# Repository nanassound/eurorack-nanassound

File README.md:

# Nanas Sound's Eurorack Modules

Modules made by Nanas Sound.
- [Mini](https://github.com/bepitulaz/eurorack-nanassound/tree/main/Mini): USB-C power supply
- [Rohkem](https://github.com/bepitulaz/eurorack-nanassound/tree/main/Rohkem): 1x7 or 2x3 passive signal multiplier
- [Uksed](https://github.com/bepitulaz/eurorack-nanassound/tree/main/Uksed): 4-channels audio input module
- [EuroPlatvorm](https://github.com/bepitulaz/eurorack-nanassound/tree/main/EuroPlatvorm): ESP32-C6 motherboard with GPIO and power breakout headers

## License

Hardware is licensed under [CC BY-SA 4.0](https://creativecommons.org/licenses/by-sa/4.0/).

By [Asep Bagja](https://www.asepbagja.com/)

Contact: [asep@nanas.ee](mailto:asep@nanas.ee)

© 2026 Nanas Sound OÜ

## Guidelines for derivative works

**Nanas Sound** is a business name of [Nanas Sound OÜ](https://ariregister.rik.ee/est/company/16028176/Nanas-Sound-OÜ).

You should not use Nanas Sound name, logo, or any other identifiers on your derivative works you create from files in this repository.

For example, your adaptation of Nanas Sound's Mini should be named "Strawberry Field - Mini Fruity" or similar.

You should include a visible license notice as required by the terms of the CC BY-SA 4.0 license.

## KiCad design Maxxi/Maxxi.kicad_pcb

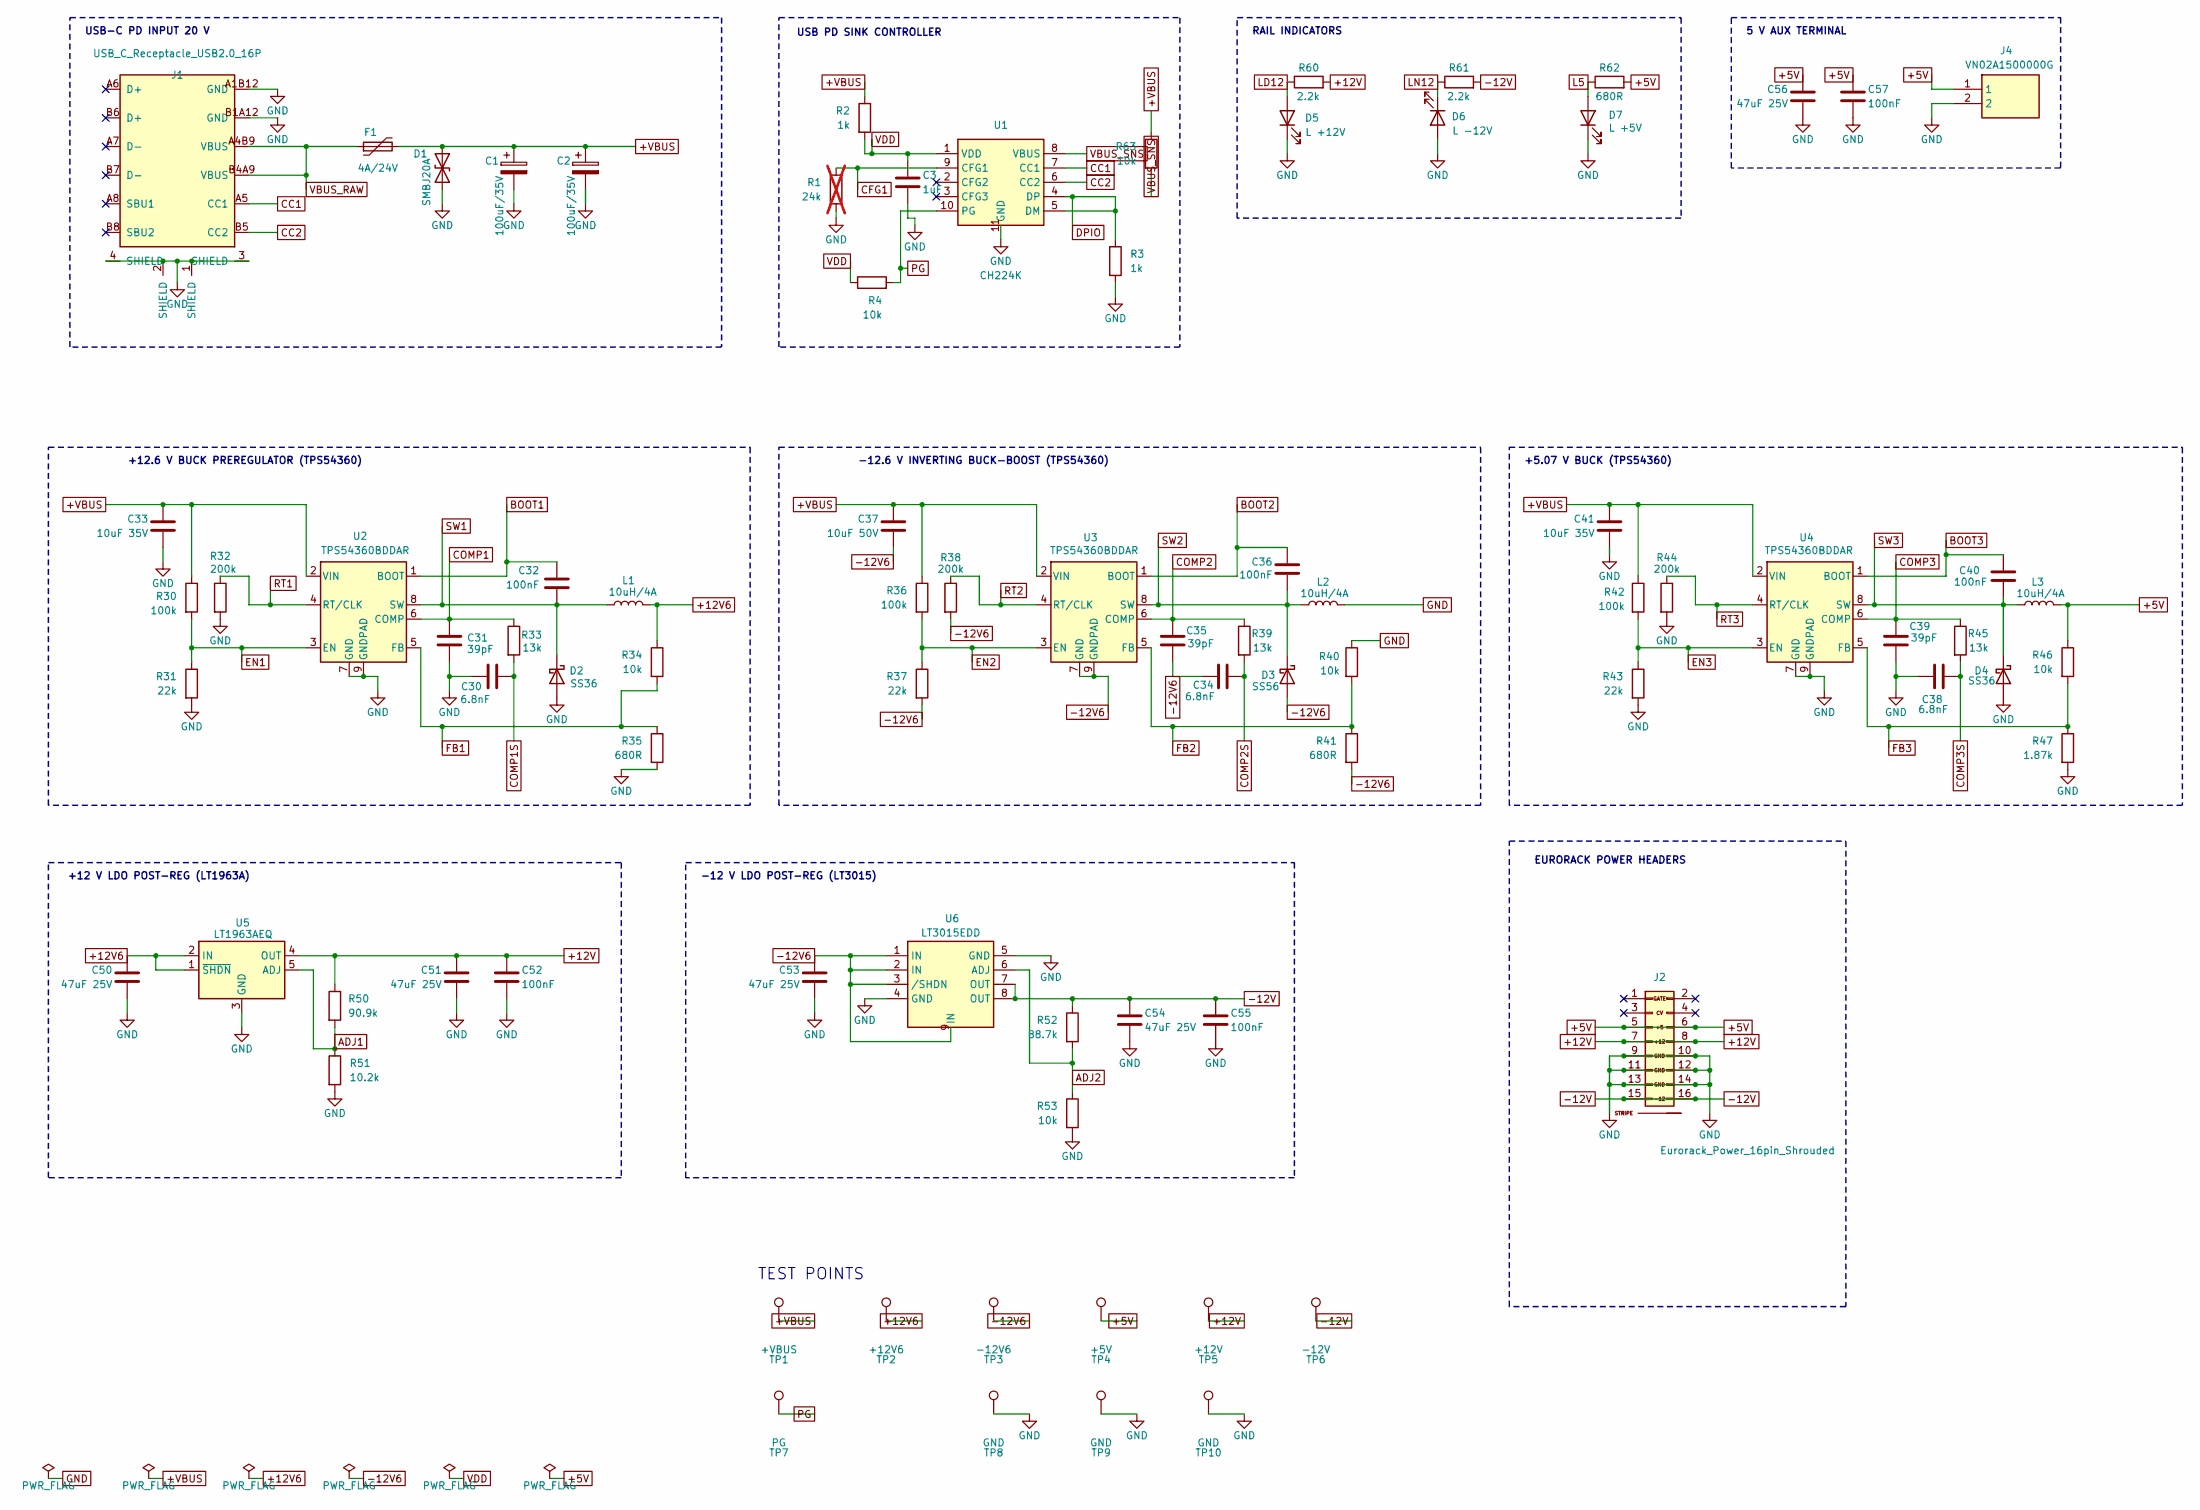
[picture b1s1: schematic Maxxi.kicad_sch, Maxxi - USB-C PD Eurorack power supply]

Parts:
C1, C2: 100uF/35V; CP_Elec_6.3x7.7; Manufacturer_Part_Number RVT1V101M0607; LCSC Part Number C72478
C3: 1uF; C_0603_1608Metric; Manufacturer_Part_Number CL10B105KA8NNNC; LCSC Part Number C29936
C30, C34, C38: 6.8nF; C_0603_1608Metric; Manufacturer_Part_Number CC0603KRX7R9BB683; LCSC Part Number C107098
C31, C35, C39: 39pF; C_0603_1608Metric; Manufacturer_Part_Number CL10C390JB81PNC; LCSC Part Number C472792
C32, C36, C40, C52, C55, C57: 100nF; C_0603_1608Metric; Manufacturer_Part_Number CC0603KRX7R9BB104; LCSC Part Number C14663
C33, C41: 10uF 35V; C_1206_3216Metric; Manufacturer_Part_Number 1206X7S106K350NT; LCSC Part Number C49326788
C37: 10uF 50V; C_1206_3216Metric; Manufacturer_Part_Number 1206X7R106K500NT; LCSC Part Number C49326770
C50, C51, C53, C54, C56: 47uF 25V; C_1206_3216Metric; Manufacturer_Part_Number GRM31CR61E476ME44L; LCSC Part Number C403725
D1: SMBJ20A; D_SMB; Manufacturer_Part_Number SMBJ20A; LCSC Part Number C353377
D2, D4: SS36; D_SMA; Manufacturer_Part_Number SS36; LCSC Part Number C16015
D3: SS56; D_SMA; Manufacturer_Part_Number SS56; LCSC Part Number C65009
D5: L +12V; LED_D2.0mm_W4.8mm_H2.5mm_FlatTop; Manufacturer_Part_Number C6717903 LED; LCSC Part Number C6717903
D6: L -12V; LED_D2.0mm_W4.8mm_H2.5mm_FlatTop; Manufacturer_Part_Number C6717903 LED; LCSC Part Number C6717903
D7: L +5V; LED_D2.0mm_W4.8mm_H2.5mm_FlatTop; Manufacturer_Part_Number C6717903 LED; LCSC Part Number C6717903
F1: 4A/24V; Fuse_1812_4532Metric; Manufacturer_Part_Number 1812L400/24GR; LCSC Part Number C42435780
J1: USB_C_Receptacle_USB2.0_16P; USB-C_SMD_LAIL-TYPE-C-16PIN-05-LT; Manufacturer_Part_Number LAIL-TYPE-C-16PIN-05-LT; LCSC Part Number C55591234
J2: Eurorack_Power_16pin_Shrouded; Pins_2x08_2.54mm_TH_EuroPower_Shrouded_reducedsilk; Part Number LL1007-1 (2*8 HITEMP)
J4: VN02A1500000G; Manufacturer_Part_Number VN02A1500000G; LCSC Part Number C5188442
L1, L2, L3: 10uH/4A; IND-SMD_L8.0-W8.0_SMNR8040; Manufacturer_Part_Number SWPA8040S100MT; LCSC Part Number C37429
R1: 24k; R_0603_1608Metric; Manufacturer_Part_Number RC0603FR-0724KL; not fitted
R2: 1k; R_1210_3225Metric; Manufacturer_Part_Number RC1210FR-071KP; LCSC Part Number C20164422
R3: 1k; R_0603_1608Metric; Manufacturer_Part_Number FRC0603F1001TS; LCSC Part Number C2907002
R4, R34, R40, R46, R53, R63: 10k; R_0603_1608Metric; Manufacturer_Part_Number FRC0603F1002TS; LCSC Part Number C2906982
R30, R36, R42: 100k; R_0603_1608Metric; Manufacturer_Part_Number 0603WAF1003T5E; LCSC Part Number C25803
R31, R37, R43: 22k; R_0603_1608Metric; Manufacturer_Part_Number FRC0603F2202TS; LCSC Part Number C2907015
R32, R38, R44: 200k; R_0603_1608Metric; Manufacturer_Part_Number FRC0603F2003TS; LCSC Part Number C2907009
R33, R39, R45: 13k; R_0603_1608Metric; Manufacturer_Part_Number FRC0603F1302TS; LCSC Part Number C2906992
R35, R41, R62: 680R; R_0603_1608Metric; Manufacturer_Part_Number RCA03680RFLF; LCSC Part Number C22356475
R47: 1.87k; R_0603_1608Metric; Manufacturer_Part_Number FRC0603F1871TS; LCSC Part Number C2930054
R50: 90.9k; R_0603_1608Metric; Manufacturer_Part_Number FRC0603F9092TS; LCSC Part Number C2930136
R51: 10.2k; R_0603_1608Metric; Manufacturer_Part_Number FRC0603F1022TS; LCSC Part Number C2933125
R52: 88.7k; R_0603_1608Metric; Manufacturer_Part_Number FRC0603F8872TS; LCSC Part Number C2999456
R60, R61: 2.2k; R_0603_1608Metric; Manufacturer_Part_Number FRC0603F2201TS; LCSC Part Number C2907005
TP1: +VBUS; TestPoint_Pad_D1.5mm
TP2: +12V6; TestPoint_Pad_D1.5mm
TP3: -12V6; TestPoint_Pad_D1.5mm
TP4: +5V; TestPoint_Pad_D1.5mm
TP5: +12V; TestPoint_Pad_D1.5mm
TP6: -12V; TestPoint_Pad_D1.5mm
TP7: PG; TestPoint_Pad_D1.5mm
TP8, TP9, TP10: GND; TestPoint_Pad_D1.5mm
U1: CH224K; ESSOP-10_L4.9-W3.9-P1.0-LS6.0-TL-EP; Manufacturer_Part_Number CH224K; LCSC Part Number C970725
U2, U3, U4: TPS54360BDDAR; SOIC-8-1EP_3.9x4.9mm_P1.27mm_EP2.71x3.7mm_ThermalVias; Manufacturer_Part_Number TPS54360BDDAR; LCSC Part Number C524806
U5: LT1963AEQ; TO-263-5_TabPin3; Manufacturer_Part_Number LT1963AEQ; LCSC Part Number C459702
U6: LT3015EDD; DFN-8_L3.0-W3.0-P0.50-TL-EP; Manufacturer_Part_Number LT3015EDD; LCSC Part Number C117305

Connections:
+5V: C56.1, C57.1, J2.5 (+12V), J2.6, J4.1, L3.2, R46.1, R62.2, TP4.1 (1_1)
+12V: C51.1, C52.1, J2.7 (12V), J2.8 (+12V), R50.1, R60.2, TP5.1 (1_1), U5.4 (OUT)
+12V6: C50.1, L1.2, R34.1, TP2.1 (1_1), U5.1 (~SHDN), U5.2 (IN)
+VBUS: C1.1, C2.1, C33.1, C37.1, C41.1, D1.1 (A1), F1.2, R2.1, R30.1, R36.1, R42.1, R63.1, TP1.1 (1_1), U2.2 (VIN), U3.2 (VIN), U4.2 (VIN)
-12V: C54.1, C55.1, J2.15 (-12V), J2.16, R52.1, R61.2, TP6.1 (1_1), U6.7 (OUT), U6.8 (OUT)
-12V6: C34.1, C35.2, C37.2, C53.1, D3.2 (A), R37.2, R38.2, R41.2, TP3.1 (1_1), U3.7 (GND), U3.9 (GNDPAD), U6.1 (IN), U6.2 (IN), U6.3 (/SHDN), U6.9 (IN)
ADJ1: R50.2, R51.1, U5.5 (ADJ)
ADJ2: R52.2, R53.1, U6.6 (ADJ)
BOOT1: C32.1, U2.1 (BOOT)
BOOT2: C36.1, U3.1 (BOOT)
BOOT3: C40.1, U4.1 (BOOT)
CC1: J1.A5 (CC1), U1.7 (CC1)
CC2: J1.B5 (CC2), U1.6 (CC2)
CFG1: R1.1, U1.9 (CFG1)
COMP1: C31.1, R33.1, U2.6 (COMP)
COMP1S: C30.2, R33.2
COMP2: C35.1, R39.1, U3.6 (COMP)
COMP2S: C34.2, R39.2
COMP3: C39.1, R45.1, U4.6 (COMP)
COMP3S: C38.2, R45.2
DPIO: R3.1, U1.4 (DP), U1.5 (DM)
EN1: R30.2, R31.1, U2.3 (EN)
EN2: R36.2, R37.1, U3.3 (EN)
EN3: R42.2, R43.1, U4.3 (EN)
FB1: R34.2, R35.1, U2.5 (FB)
FB2: R40.2, R41.1, U3.5 (FB)
FB3: R46.2, R47.1, U4.5 (FB)
GND: C1.2, C2.2, C3.2, C30.1, C31.2, C33.2, C38.1, C39.2, C41.2, C50.2, C51.2, C52.2, C53.2, C54.2, C55.2, C56.2, C57.2, D1.2 (A2), D2.2 (A), D4.2 (A), D5.1 (K), D6.2 (A), D7.1 (K), J1.1 (SHIELD), J1.2 (SHIELD), J1.3 (SHIELD), J1.4 (SHIELD), J1.A1B12 (GND), J1.B1A12 (GND), J2.9 (GND), J2.10 (GND), J2.11 (GND), J2.12 (GND), J2.13 (-12), J2.14 (-12V), J4.2, L2.2, R1.2, R3.2, R31.2, R32.2, R35.2, R40.1, R43.2, R44.2, R47.2, R51.2, R53.2, TP8.1 (1_1), TP9.1 (1_1), TP10.1 (1_1), U1.11 (GND), U2.7 (GND), U2.9 (GNDPAD), U4.7 (GND), U4.9 (GNDPAD), U5.3 (GND), U6.4 (GND), U6.5 (GND)
L5: D7.2 (A), R62.1
LD12: D5.2 (A), R60.1
LN12: D6.1 (K), R61.1
PG: R4.2, TP7.1 (1_1), U1.10 (PG)
RT1: R32.1, U2.4 (RT/CLK)
RT2: R38.1, U3.4 (RT/CLK)
RT3: R44.1, U4.4 (RT/CLK)
SW1: C32.2, D2.1 (K), L1.1, U2.8 (SW)
SW2: C36.2, D3.1 (K), L2.1, U3.8 (SW)
SW3: C40.2, D4.1 (K), L3.1, U4.8 (SW)
VBUS_RAW: F1.1, J1.A4B9 (VBUS), J1.B4A9 (VBUS)
VBUS_SNS: R63.2, U1.8 (VBUS)
VDD: C3.1, R2.2, R4.1, U1.1 (VDD)

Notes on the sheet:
+12 V LDO POST-REG (LT1963A)
EURORACK POWER HEADERS
TEST POINTS
-12.6 V INVERTING BUCK-BOOST (TPS54360)
USB-C PD INPUT 20 V
-12 V LDO POST-REG (LT3015)
RAIL INDICATORS
USB PD SINK CONTROLLER
+5.07 V BUCK (TPS54360)
5 V AUX TERMINAL
+12.6 V BUCK PREREGULATOR (TPS54360)

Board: 2 copper layers, 83 parts (1 on the bottom side), 41 nets, no tracks yet.

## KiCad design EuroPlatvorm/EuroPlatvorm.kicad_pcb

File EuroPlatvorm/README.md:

# EuroPlatvorm: ESP32-C6 Eurorack Motherboard

EuroPlatvorm brings an ESP32-C6 into a Eurorack case. It is a carrier board for stacking daughter boards: two 1x14 pin headers on the back pass GPIO pins and power rails straight through.

| Top | Bottom |
|-----|--------|
|  |  |

## Features

- ESP32-C6-WROOM-1-N4 module with native USB for flashing and serial
- USB-C port for programming and power
- Eurorack +12V power input through a 2x5 header
- Two 1x14 stacking headers (J3, J4) carrying 3V3, +12V, -12V, GND and 24 GPIO pins
- RST and BOOT push buttons
- Green power LED

## Board

| Spec | Value |
|------|-------|
| Size | 89.75 x 21.7 mm |
| Layers | 4 (top and bottom signal, inner 1 is a GND plane, inner 2 is a +3V3 plane) |
| Components | 34 (25 BOM lines) |
| CAD | KiCad 10, files in this folder |

Top of the board carries the power section, USB-C, buttons and the ESP32 module. The two carrier headers are through-hole parts on the bottom side, so daughter boards stack behind the board.

## Power

Both regulators feed the same +3V3 rail. The buck sets 3.31 V from the feedback divider (VFB 0.596 V, R1 100k, R2 22k). Reverse polarity on the eurorack ribbon is blocked by the SS34 diode; both inputs are fused with resettable 500 mA PTCs.

Running from eurorack power puts about 2.7 V back onto the USB VBUS line through the AMS1117 reverse path. The F2 PTC limits that current. Use one power source at a time to keep VBUS clean.

The -12V rail from the eurorack bus passes to J3 pin 3 for daughter boards. The onboard logic runs entirely on +3V3.

## Connectors

### J1: Eurorack power, 2x5

| Pin | Net | Pin | Net |
|-----|-----|-----|-----|
| 1 | -12V | 2 | -12V |
| 3 | GND | 4 | GND |
| 5 | GND | 6 | GND |
| 7 | GND | 8 | GND |
| 9 | +12V | 10 | +12V |

### J3: carrier header left, 1x14

| Pin | Net | Pin | Net |
|-----|-----|-----|-----|
| 1 | +3V3 | 8 | GPIO4 |
| 2 | +12V | 9 | GPIO5 |
| 3 | -12V | 10 | GPIO6 |
| 4 | GPIO0 | 11 | GPIO7 |
| 5 | GPIO1 | 12 | USB_DP |
| 6 | GPIO2 | 13 | USB_DM |
| 7 | GPIO3 | 14 | GND |

### J4: carrier header right, 1x14

| Pin | Net | Pin | Net |
|-----|-----|-----|-----|
| 1 | GPIO23 | 8 | GPIO16 |
| 2 | GPIO22 | 9 | GPIO15 |
| 3 | GPIO21 | 10 | GPIO11 |
| 4 | GPIO20 | 11 | GPIO10 |
| 5 | GPIO19 | 12 | GPIO9 |
| 6 | GPIO18 | 13 | GPIO8 |
| 7 | GPIO17 | 14 | GND |

USB_DP and USB_DM on J3 are the same nets as the USB-C data lines (ESP32-C6 GPIO12 / GPIO13). A daughter board can expose a second USB port on them, and doing so shares the port with J2.

### J2: USB-C

USB 2.0 receptacle used for flashing and power. CC1 and CC2 carry 5.1k pull-downs. Data lines pass through a USBLC6-2SC6 ESD protector to the ESP32-C6 native USB peripheral.

## Buttons and LED

| Ref | Function |
|-----|----------|
| SW1 (RST) | Pulls ESP32 EN low, resets the chip |
| SW2 (BOOT) | Pulls GPIO9 low, enters download mode for flashing |
| D2 | Green power indicator on +3V3, 1k series resistor |

## Files

| Path | Contents |
|------|----------|
| `EuroPlatvorm.kicad_sch`, `EuroPlatvorm.kicad_pcb` | Schematic and PCB source |
| `fabrication/` | JLCPCB-ready gerbers, drill files, `EuroPlatvorm-BOM.csv`, `EuroPlatvorm-CPL.csv` |
| `datasheets/` | PDFs for TPS54202, AMS1117, USBLC6-2SC6, ESP32-C6-WROOM-1, the power header, USB-C |

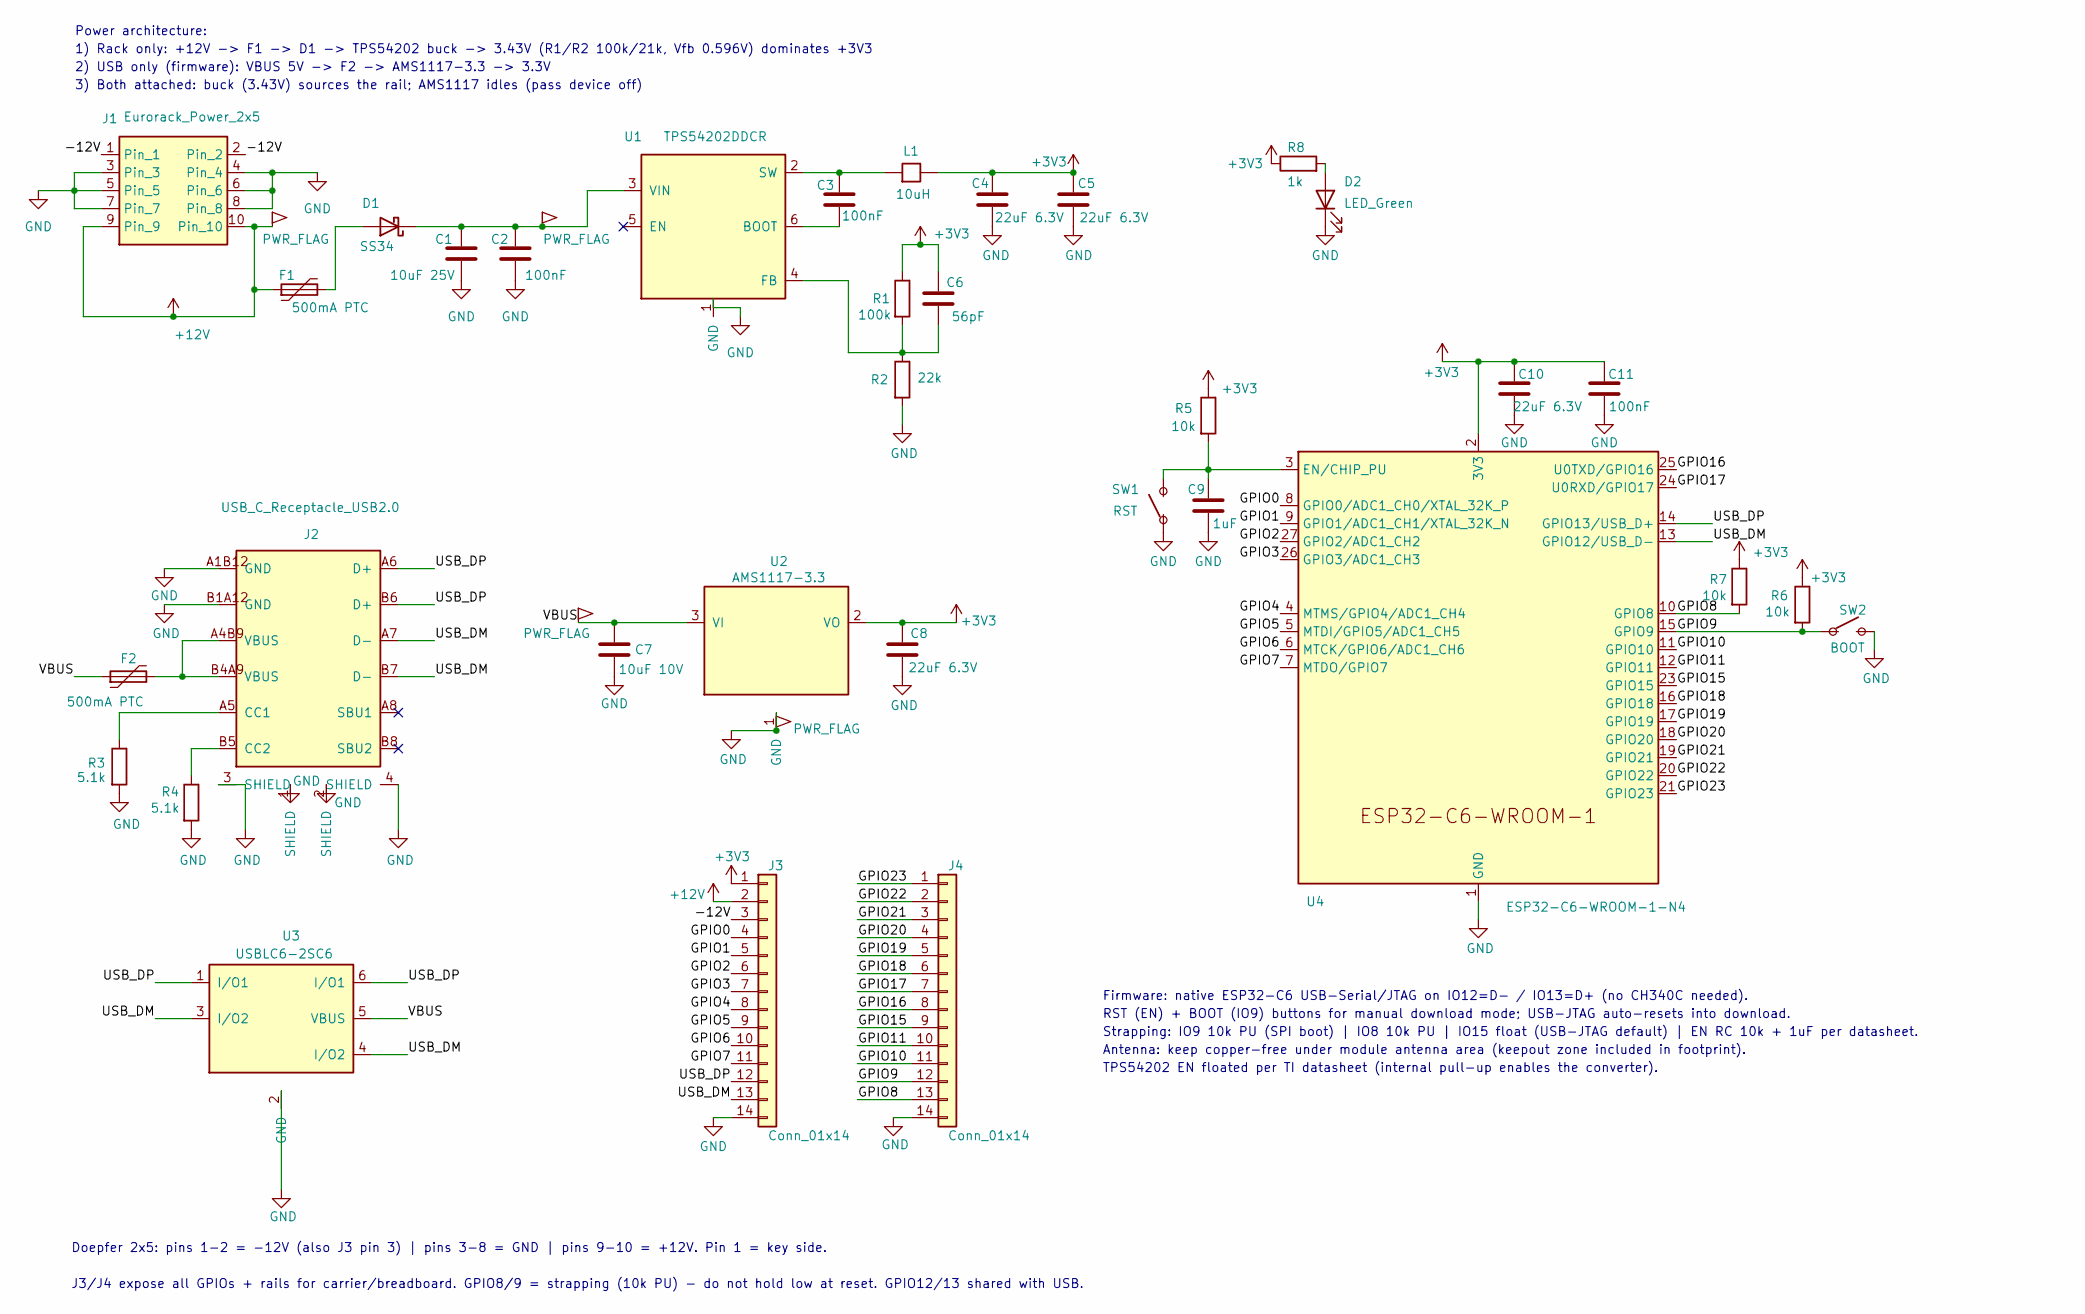
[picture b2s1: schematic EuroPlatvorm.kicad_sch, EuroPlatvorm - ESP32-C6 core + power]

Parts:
C1: 10uF 25V; C_1206_3216Metric; MPN CL31A106KAHNNNE; LCSC C9807
C2, C3: 100nF; C_0603_1608Metric; MPN CC0603KRX7R9BB104; LCSC C14663
C4, C5, C8, C10: 22uF 6.3V; C_0805_2012Metric; MPN CL21A226MQQNNNE; LCSC C5674
C6: 56pF; C_0603_1608Metric; MPN CL10C560JB8NNNC; LCSC C39148
C7: 10uF 10V; C_0805_2012Metric; MPN CL21A106KPCLQNC; LCSC C962097
C9: 1uF; C_0603_1608Metric; MPN CL10A105KO8NNNC; LCSC C1592
C11: 100nF; C_0402_1005Metric; MPN CL05B104KB5NNNC; LCSC C307331
D1: SS34; D_SMA; MPN SS34; LCSC C8678
D2: LED_Green; LED_0603_1608Metric; MPN XL-1608UGC-04; LCSC C965804
F1, F2: 500mA PTC; Fuse_1206_3216Metric; MPN 1206L050/30NR; LCSC C7542947
J1: Eurorack_Power_2x5; PinHeader_2x05_P2.54mm_Vertical; MPN PZ254V-12-10P; LCSC C492422
J2: USB_C_Receptacle_USB2.0; USB-C_SMD-TYPE-C-31-M-12_1; MPN TYPE-C-31-M-12; LCSC C165948
J3, J4: Conn_01x14; PinHeader_1x14_P2.54mm_Vertical; MPN 2.54-1x40P; LCSC C2337
L1: 10uH; IND-SMD_L6.0-W6.0; MPN YNR6045-100M; LCSC C341067
R1: 100k; R_0603_1608Metric; MPN 0603WAF1003T5E; LCSC C25803
R2: 22k; R_0603_1608Metric; MPN FRC0603F2202TS; LCSC C2907015
R3, R4: 5.1k; R_0603_1608Metric; MPN 0603WAF5101T5E; LCSC C23186
R5, R6, R7: 10k; R_0603_1608Metric; MPN FRC0603F1002TS; LCSC C2906982
R8: 1k; R_0603_1608Metric; MPN 0603WAF1001T5E; LCSC C21190
SW1: RST; SW_TS-1187A; MPN TS-1187A-B-A-B; LCSC C318884
SW2: BOOT; SW_TS-1187A; MPN TS-1187A-B-A-B; LCSC C318884
U1: TPS54202DDCR; SOT-23-6; MPN TPS54202DDCR; LCSC C191884
U2: AMS1117-3.3; SOT-223-3_TabPin2; MPN AMS1117-3.3; LCSC C6186
U3: USBLC6-2SC6; SOT-23-6; MPN USBLC6-2SC6; LCSC C7519
U4: ESP32-C6-WROOM-1-N4; ESP32-C6-WROOM-1; MPN ESP32-C6-WROOM-1-N4; LCSC C6034714

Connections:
+3V3: C4.1, C5.1, C6.1, C8.1, C10.2, C11.2, J3.1, L1.2, R1.1, R5.1, R6.1, R7.1, R8.1, U2.2 (VO), U4.2 (3V3)
+12V: F1.1, J1.9, J1.10, J3.2
/-12V: J1.1, J1.2, J3.3
/GPIO0: J3.4, U4.8 (GPIO0/ADC1_CH0/XTAL_32K_P)
/GPIO1: J3.5, U4.9 (GPIO1/ADC1_CH1/XTAL_32K_N)
/GPIO2: J3.6, U4.27 (GPIO2/ADC1_CH2)
/GPIO3: J3.7, U4.26 (GPIO3/ADC1_CH3)
/GPIO4: J3.8, U4.4 (MTMS/GPIO4/ADC1_CH4)
/GPIO5: J3.9, U4.5 (MTDI/GPIO5/ADC1_CH5)
/GPIO6: J3.10, U4.6 (MTCK/GPIO6/ADC1_CH6)
/GPIO7: J3.11, U4.7 (MTDO/GPIO7)
/GPIO8: J4.13, R7.2, U4.10 (GPIO8)
/GPIO9: J4.12, R6.2, SW2.1, U4.15 (GPIO9)
/GPIO10: J4.11, U4.11 (GPIO10)
/GPIO11: J4.10, U4.12 (GPIO11)
/GPIO15: J4.9, U4.23 (GPIO15)
/GPIO16: J4.8, U4.25 (U0TXD/GPIO16)
/GPIO17: J4.7, U4.24 (U0RXD/GPIO17)
/GPIO18: J4.6, U4.16 (GPIO18)
/GPIO19: J4.5, U4.17 (GPIO19)
/GPIO20: J4.4, U4.18 (GPIO20)
/GPIO21: J4.3, U4.19 (GPIO21)
/GPIO22: J4.2, U4.20 (GPIO22)
/GPIO23: J4.1, U4.21 (GPIO23)
/USB_DM: J2.A7 (D-), J2.B7 (D-), J3.13, U3.3 (I/O2), U3.4 (I/O2), U4.13 (GPIO12/USB_D-)
/USB_DP: J2.A6 (D+), J2.B6 (D+), J3.12, U3.1 (I/O1), U3.6 (I/O1), U4.14 (GPIO13/USB_D+)
/VBUS: C7.1, F2.1, U2.3 (VI), U3.5 (VBUS)
GND: C1.2, C2.2, C4.2, C5.2, C7.2, C8.2, C9.2, C10.1, C11.1, D2.1 (K), J1.3, J1.4, J1.5, J1.6, J1.7, J1.8, J2.1 (SHIELD), J2.2 (SHIELD), J2.3 (SHIELD), J2.4 (SHIELD), J2.A1B12 (GND), J2.B1A12 (GND), J3.14, J4.14, R2.2, R3.2, R4.2, SW1.1, SW2.2, U1.1 (GND), U2.1 (GND), U3.2 (GND), U4.1 (GND), U4.28 (GND), U4.29 (GND)
unnamed: D1.2 (A), F1.2
unnamed: C1.1, C2.1, D1.1 (K), U1.3 (VIN)
unnamed: D2.2 (A), R8.2
unnamed: F2.2, J2.A4B9 (VBUS), J2.B4A9 (VBUS)
unnamed: J2.A5 (CC1), R3.1
unnamed: J2.B5 (CC2), R4.1
unnamed: C3.2, U1.6 (BOOT)
unnamed: C6.2, R1.2, R2.1, U1.4 (FB)
unnamed: C3.1, L1.1, U1.2 (SW)
unnamed: C9.1, R5.2, SW1.2, U4.3 (EN/CHIP_PU)

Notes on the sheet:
Strapping: IO9 10k PU (SPI boot) | IO8 10k PU | IO15 float (USB-JTAG default) | EN RC 10k + 1uF per datasheet.
Doepfer 2x5: pins 1-2 = -12V (also J3 pin 3) | pins 3-8 = GND | pins 9-10 = +12V. Pin 1 = key side.
J3/J4 expose all GPIOs + rails for carrier/breadboard. GPIO8/9 = strapping (10k PU) - do not hold low at reset. GPIO12/13 shared with USB.
Firmware: native ESP32-C6 USB-Serial/JTAG on IO12=D- / IO13=D+ (no CH340C needed).
RST (EN) + BOOT (IO9) buttons for manual download mode; USB-JTAG auto-resets into download.
Power architecture:
2) USB only (firmware): VBUS 5V -> F2 -> AMS1117-3.3 -> 3.3V
3) Both attached: buck (3.43V) sources the rail; AMS1117 idles (pass device off)
TPS54202 EN floated per TI datasheet (internal pull-up enables the converter).
Antenna: keep copper-free under module antenna area (keepout zone included in footprint).
1) Rack only: +12V -> F1 -> D1 -> TPS54202 buck -> 3.43V (R1/R2 100k/21k, Vfb 0.596V) dominates +3V3

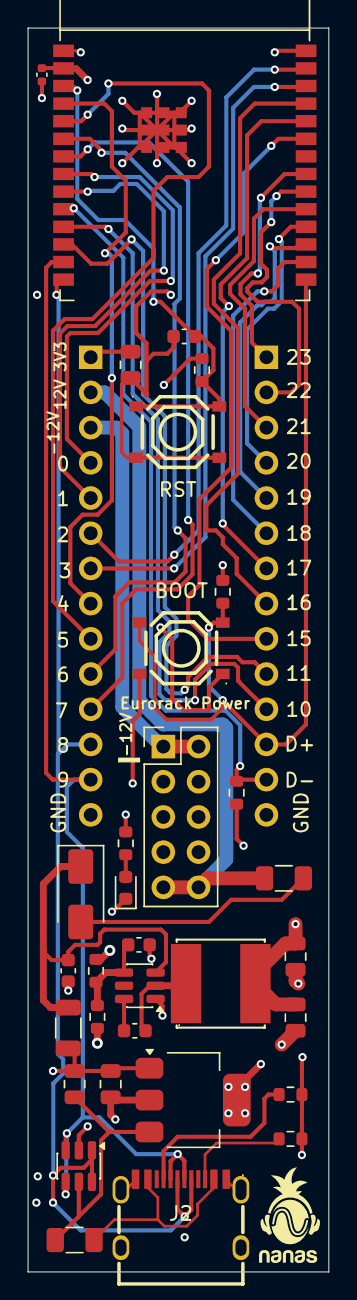
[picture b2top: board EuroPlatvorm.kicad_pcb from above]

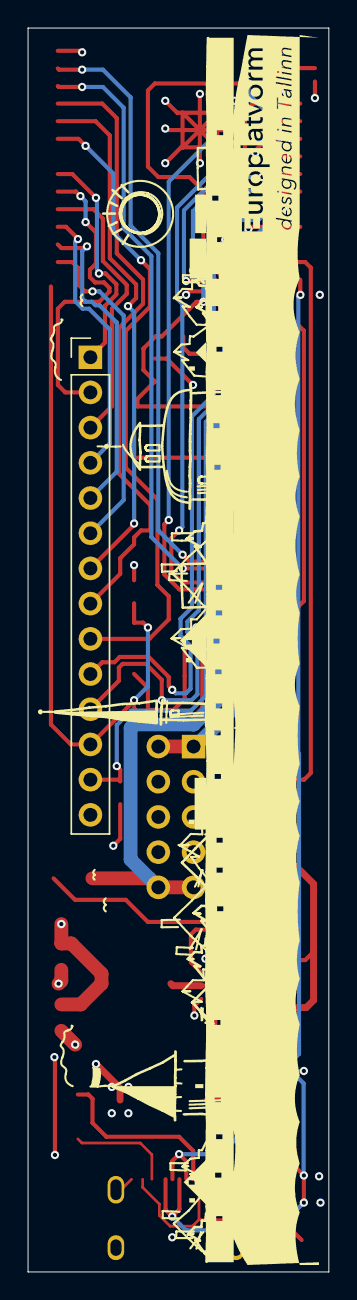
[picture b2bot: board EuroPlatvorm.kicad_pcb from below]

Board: 4 copper layers, 21.7 x 89.8 mm, 34 parts (2 on the bottom side), 38 nets.

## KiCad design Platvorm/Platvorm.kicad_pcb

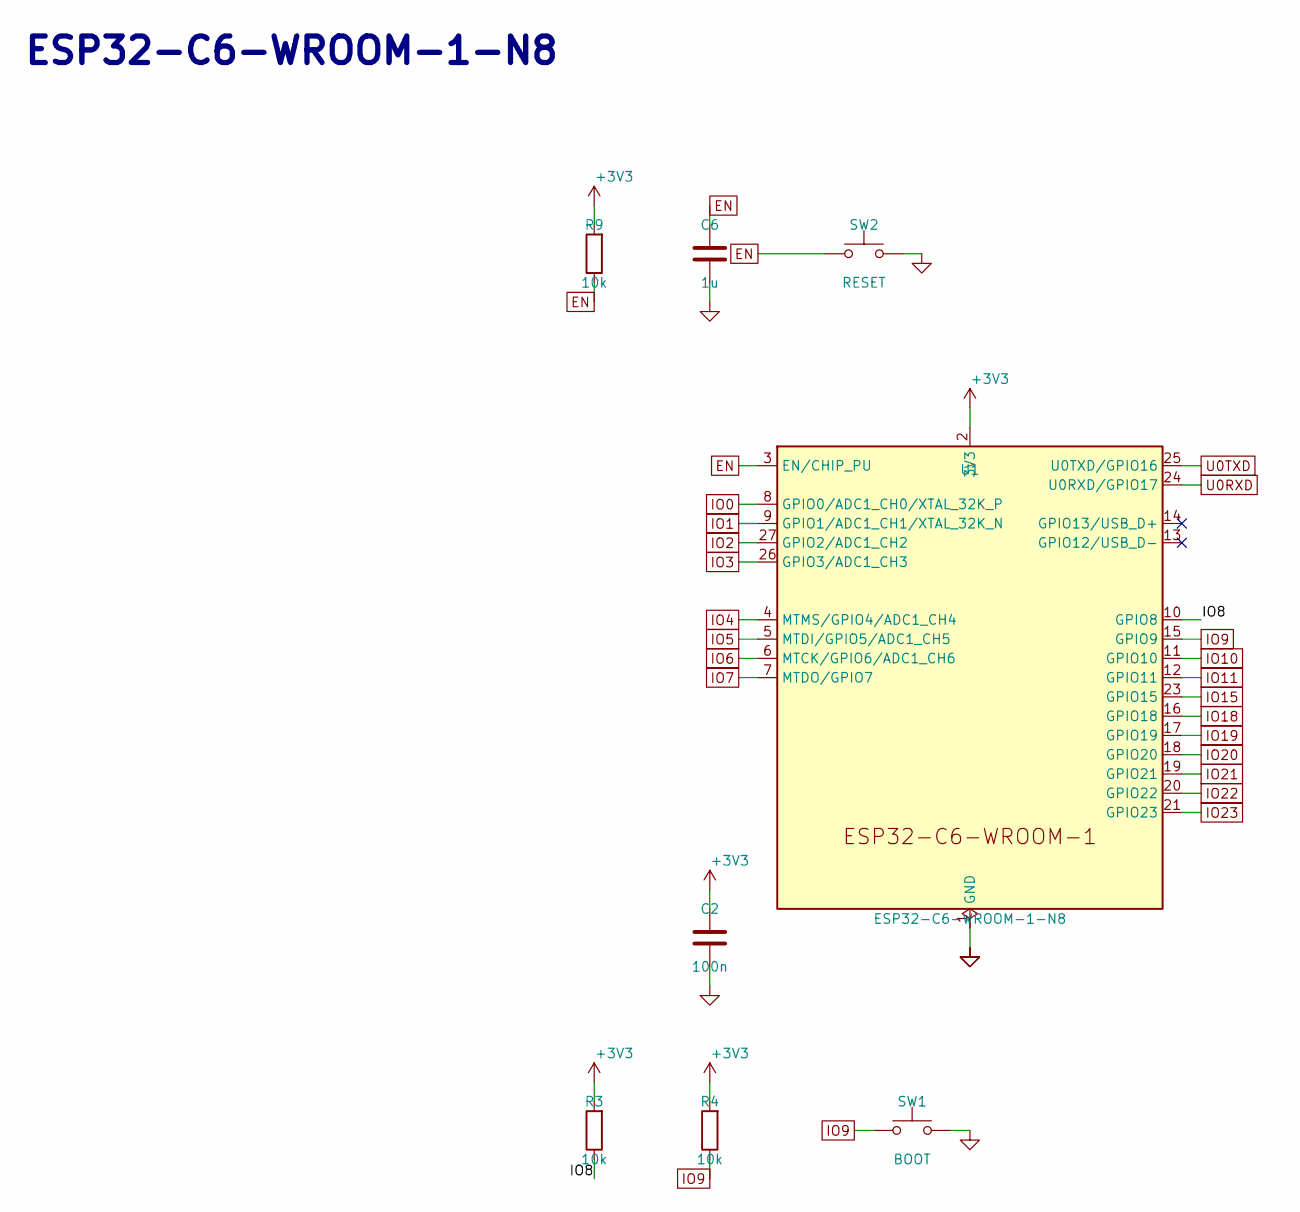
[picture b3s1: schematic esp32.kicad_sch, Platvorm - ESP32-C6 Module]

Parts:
C2: 100n; C_0402_1005Metric; MPN CL05B104KO5NNNC; LCSC C1525
C6: 1u; C_0402_1005Metric; MPN CL05A105KA5NNNC; LCSC C52923
R3, R4, R9: 10k; R_0402_1005Metric; MPN RC0402FR-0710KL; LCSC C25744
SW1: BOOT; SW_TS-1187A; MPN TS-1187A-B-A-B; LCSC C318884
SW2: RESET; SW_TS-1187A; MPN TS-1187A-B-A-B; LCSC C318884
U1: ESP32-C6-WROOM-1-N8; ESP32-C6-WROOM-1; MPN ESP32-C6-WROOM-1-N8; LCSC C5366877

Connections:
/ESP32-C6 Module/IO8: R3.1, U1.10 (GPIO8)
EN: C6.1, R9.1, SW2.1, U1.3 (EN/CHIP_PU); also elsewhere on the board
GND: C2.2, C6.2, SW1.2, SW2.2, U1.1 (GND), U1.28 (GND), U1.29 (GND); also elsewhere on the board
IO0: U1.8 (GPIO0/ADC1_CH0/XTAL_32K_P); also elsewhere on the board
IO1: U1.9 (GPIO1/ADC1_CH1/XTAL_32K_N); also elsewhere on the board
IO2: U1.27 (GPIO2/ADC1_CH2); also elsewhere on the board
IO3: U1.26 (GPIO3/ADC1_CH3); also elsewhere on the board
IO4: U1.4 (MTMS/GPIO4/ADC1_CH4); also elsewhere on the board
IO5: U1.5 (MTDI/GPIO5/ADC1_CH5); also elsewhere on the board
IO6: U1.6 (MTCK/GPIO6/ADC1_CH6); also elsewhere on the board
IO7: U1.7 (MTDO/GPIO7); also elsewhere on the board
IO9: R4.1, SW1.1, U1.15 (GPIO9); also elsewhere on the board
IO10: U1.11 (GPIO10); also elsewhere on the board
IO11: U1.12 (GPIO11); also elsewhere on the board
IO15: U1.23 (GPIO15); also elsewhere on the board
IO18: U1.16 (GPIO18); also elsewhere on the board
IO19: U1.17 (GPIO19); also elsewhere on the board
IO20: U1.18 (GPIO20); also elsewhere on the board
IO21: U1.19 (GPIO21); also elsewhere on the board
IO22: U1.20 (GPIO22); also elsewhere on the board
IO23: U1.21 (GPIO23); also elsewhere on the board
U0RXD: U1.24 (U0RXD/GPIO17); also elsewhere on the board
U0TXD: U1.25 (U0TXD/GPIO16); also elsewhere on the board

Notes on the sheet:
ESP32-C6-WROOM-1-N8

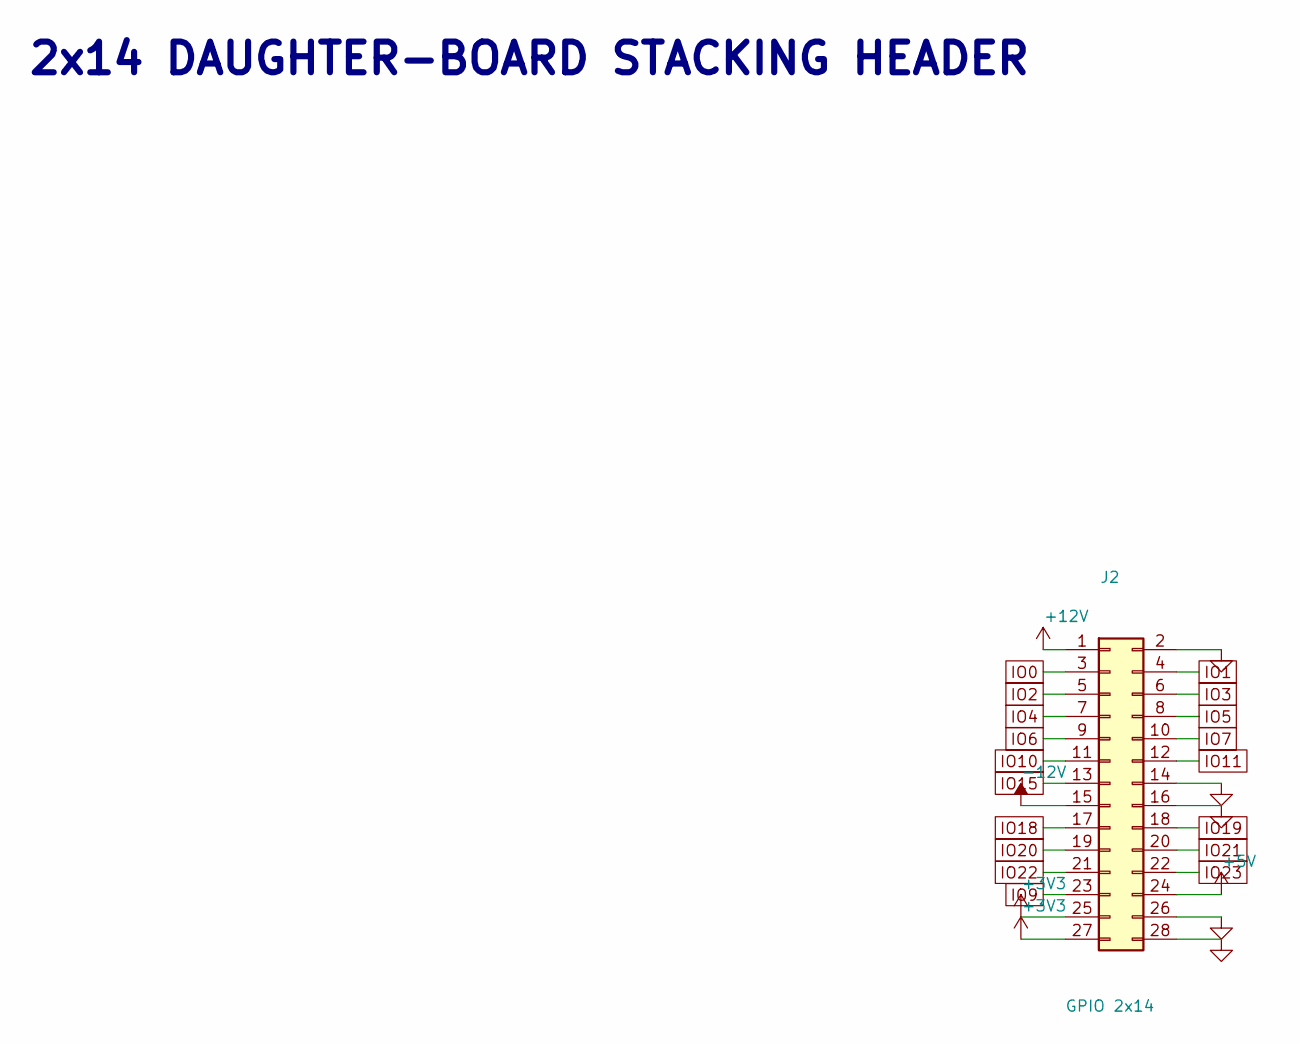
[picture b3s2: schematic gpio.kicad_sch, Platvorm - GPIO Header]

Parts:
J2: GPIO 2x14; PinHeader_2x14_P2.54mm_Vertical; MPN PZ254V-12-28P; LCSC C22465888

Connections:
GND: J2.2, J2.14, J2.16, J2.26, J2.28; also elsewhere on the board
IO0: J2.3; also elsewhere on the board
IO1: J2.4; also elsewhere on the board
IO2: J2.5; also elsewhere on the board
IO3: J2.6; also elsewhere on the board
IO4: J2.7; also elsewhere on the board
IO5: J2.8; also elsewhere on the board
IO6: J2.9; also elsewhere on the board
IO7: J2.10; also elsewhere on the board
IO9: J2.23; also elsewhere on the board
IO10: J2.11; also elsewhere on the board
IO11: J2.12; also elsewhere on the board
IO15: J2.13; also elsewhere on the board
IO18: J2.17; also elsewhere on the board
IO19: J2.18; also elsewhere on the board
IO20: J2.19; also elsewhere on the board
IO21: J2.20; also elsewhere on the board
IO22: J2.21; also elsewhere on the board
IO23: J2.22; also elsewhere on the board

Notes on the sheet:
2x14 DAUGHTER-BOARD STACKING HEADER

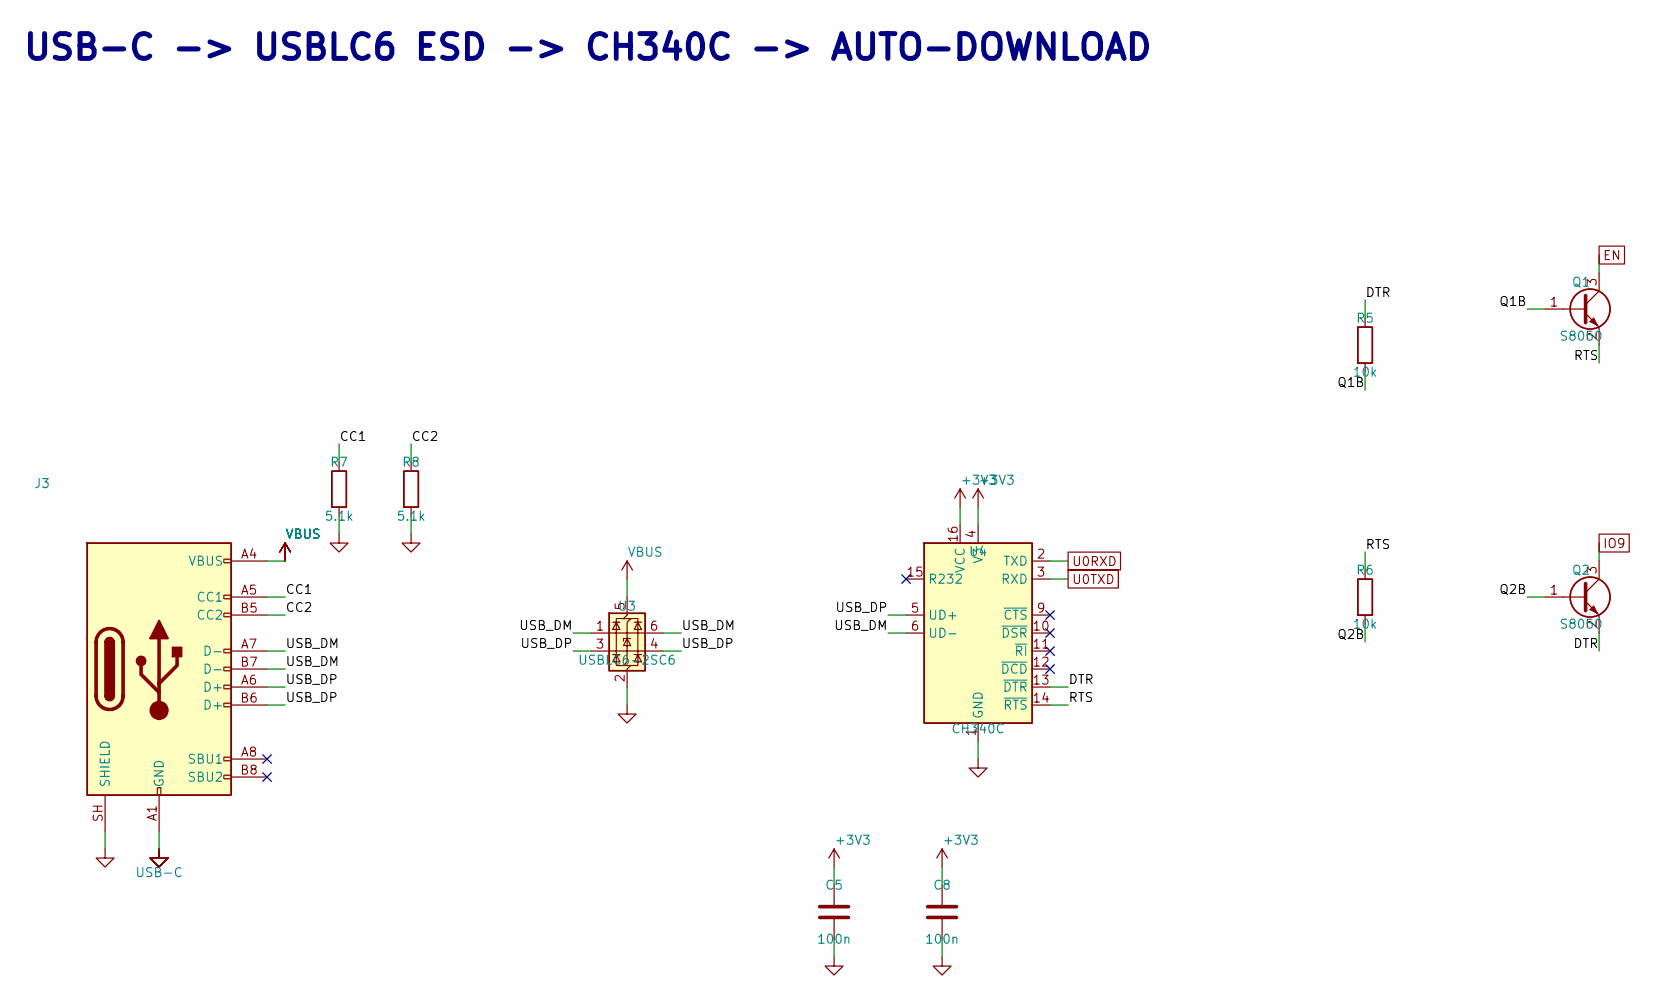
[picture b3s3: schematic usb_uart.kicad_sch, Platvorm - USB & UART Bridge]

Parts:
C5, C8: 100n; C_0402_1005Metric; MPN CL05B104KO5NNNC; LCSC C1525
J3: USB-C; USB-C_SMD-TYPE-C-31-M-12_1; MPN TYPE-C-31-M-12; LCSC C165948
Q1, Q2: S8050; SOT-23; MPN S8050; LCSC C2146
R5, R6: 10k; R_0402_1005Metric; MPN RC0402FR-0710KL; LCSC C25744
R7, R8: 5.1k; R_0402_1005Metric; MPN RC0402FR-075K1L; LCSC C25905
U3: USBLC6-2SC6; SOT-23-6; MPN USBLC6-2SC6; LCSC C2687116
U4: CH340C; SOP-16_4.4x10.4mm_P1.27mm; MPN CH340C; LCSC C84681

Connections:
/USB & UART Bridge/CC1: J3.A5 (CC1), R7.1
/USB & UART Bridge/CC2: J3.B5 (CC2), R8.1
/USB & UART Bridge/DTR: Q2.2 (E), R5.1, U4.13 (~DTR)
/USB & UART Bridge/Q1B: Q1.1 (B), R5.2
/USB & UART Bridge/Q2B: Q2.1 (B), R6.2
/USB & UART Bridge/RTS: Q1.2 (E), R6.1, U4.14 (~RTS)
/USB & UART Bridge/USB_DM: J3.A7 (D-), J3.B7 (D-), U3.1 (I/O1), U3.6 (I/O1), U4.6 (UD-)
/USB & UART Bridge/USB_DP: J3.A6 (D+), J3.B6 (D+), U3.3 (I/O2), U3.4 (I/O2), U4.5 (UD+)
EN: Q1.3 (C); also elsewhere on the board
GND: C5.2, C8.2, J3.1, J3.2, J3.3, J3.4, J3.A1 (GND), J3.A1B12, J3.A12 (GND), J3.B1 (GND), J3.B1A12, J3.B12 (GND), J3.SH (SHIELD), R7.2, R8.2, U3.2 (GND), U4.1 (GND); also elsewhere on the board
IO9: Q2.3 (C); also elsewhere on the board
U0RXD: U4.2 (TXD); also elsewhere on the board
U0TXD: U4.3 (RXD); also elsewhere on the board

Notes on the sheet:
USB-C -> USBLC6 ESD -> CH340C -> AUTO-DOWNLOAD
